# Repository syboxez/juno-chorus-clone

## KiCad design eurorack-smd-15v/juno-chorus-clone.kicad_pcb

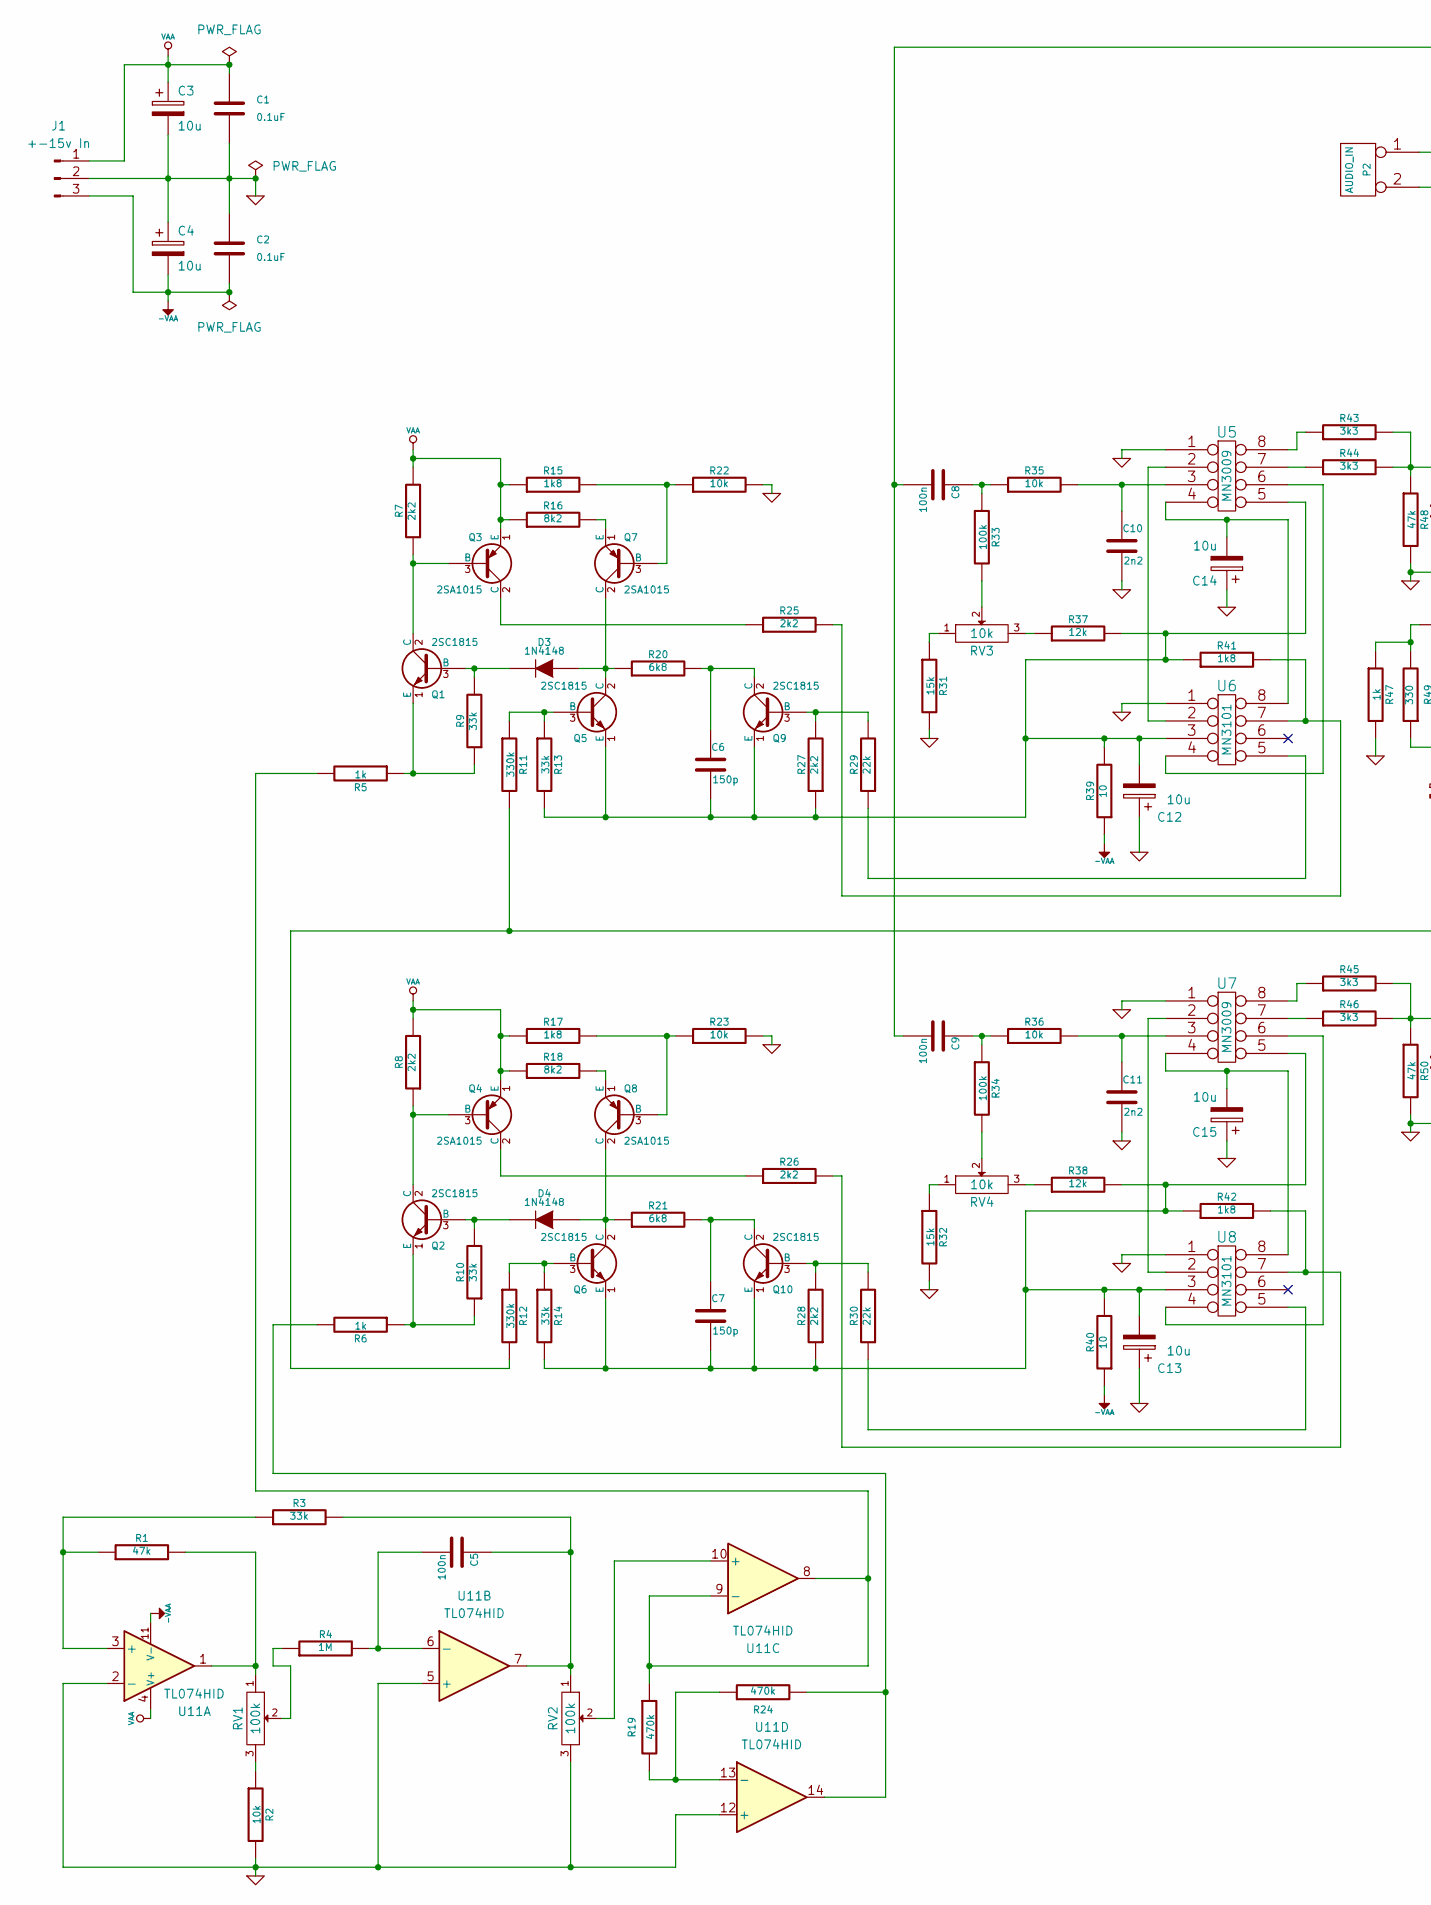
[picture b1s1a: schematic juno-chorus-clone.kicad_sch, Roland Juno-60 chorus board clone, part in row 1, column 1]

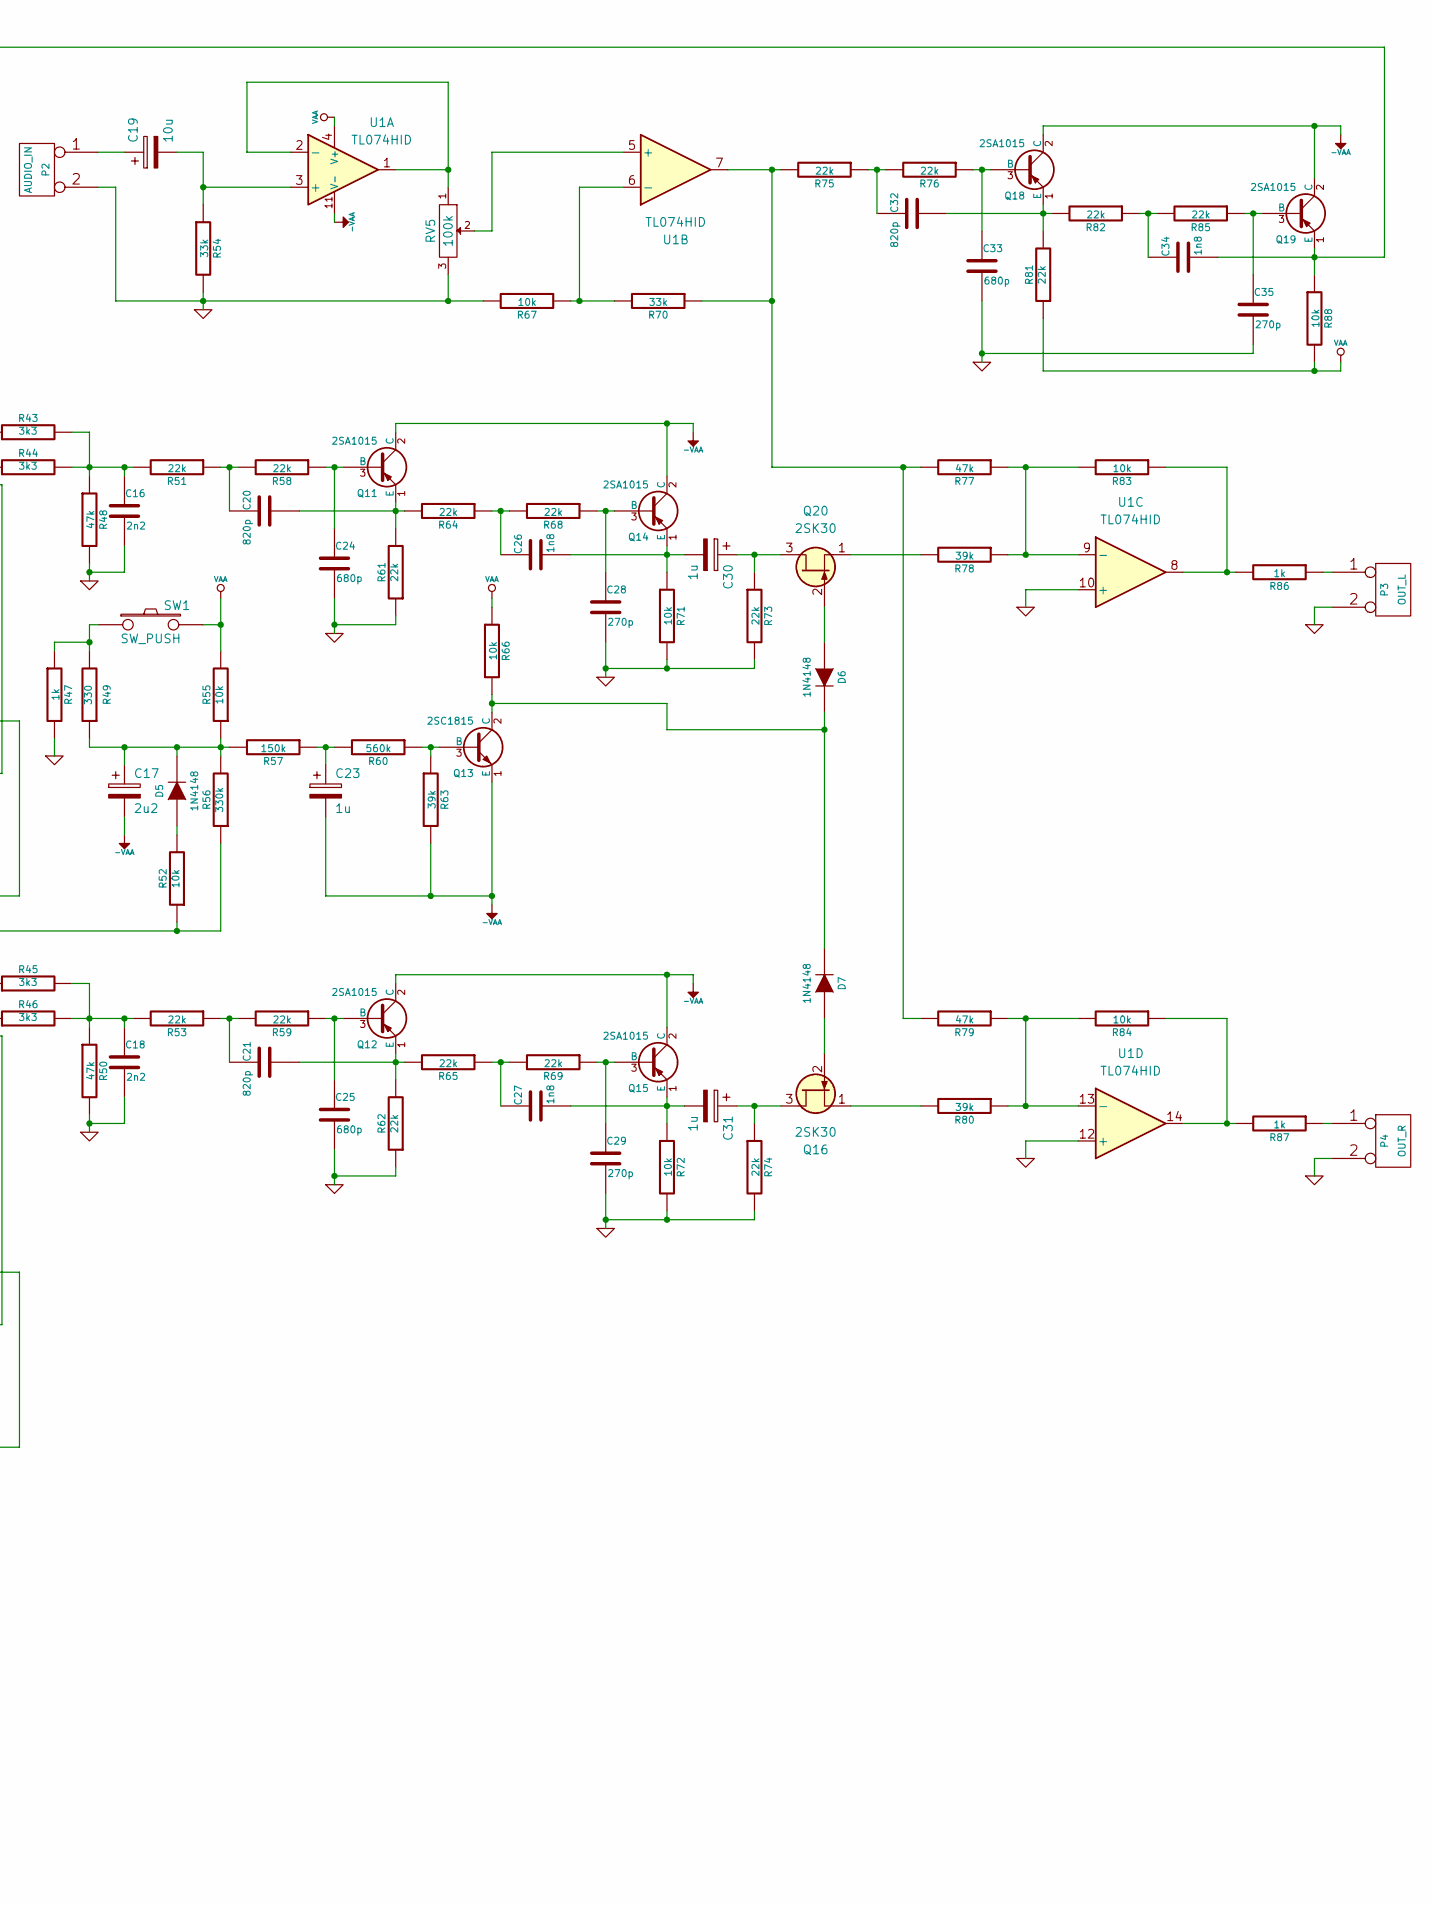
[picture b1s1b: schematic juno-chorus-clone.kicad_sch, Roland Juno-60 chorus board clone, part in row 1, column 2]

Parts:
C1, C2: 0.1uF; C_0805_2012Metric_Pad1.18x1.45mm_HandSolder
C3, C4, C12, C13, C14, C15, C19: 10u; CP_Radial_D5.0mm_P2.50mm
C5, C8, C9: 100n; C_0805_2012Metric_Pad1.18x1.45mm_HandSolder
C6, C7: 150p; C_0805_2012Metric_Pad1.18x1.45mm_HandSolder
C10, C11, C16, C18: 2n2; C_0805_2012Metric_Pad1.18x1.45mm_HandSolder
C17: 2u2; CP_Radial_D5.0mm_P2.50mm
C20, C21, C32: 820p; C_0805_2012Metric_Pad1.18x1.45mm_HandSolder
C23, C30, C31: 1u; CP_Radial_D5.0mm_P2.50mm
C24, C25, C33: 680p; C_0805_2012Metric_Pad1.18x1.45mm_HandSolder
C26, C27, C34: 1n8; C_0805_2012Metric_Pad1.18x1.45mm_HandSolder
C28, C29, C35: 270p; C_0805_2012Metric_Pad1.18x1.45mm_HandSolder
D3, D4, D5, D6, D7: 1N4148; D_0805_2012Metric_Pad1.15x1.40mm_HandSolder
J1: +-15v In; JST_XH_B3B-XH-A_1x03_P2.50mm_Vertical
P2: AUDIO_IN; JST_XH_B2B-XH-A_1x02_P2.50mm_Vertical
P3: OUT_L; JST_XH_B2B-XH-A_1x02_P2.50mm_Vertical
P4: OUT_R; JST_XH_B2B-XH-A_1x02_P2.50mm_Vertical
Q1, Q2, Q5, Q6, Q9, Q10, Q13: 2SC1815; TO-92_Inline_Wide
Q3, Q4, Q7, Q8, Q11, Q12, Q14, Q15, Q18, Q19: 2SA1015; TO-92_Inline_Wide
Q16, Q20: 2SK30; TO-92_Inline_Wide_SGD
R1, R48, R50, R77, R79: 47k; R_0805_2012Metric_Pad1.20x1.40mm_HandSolder
R2, R22, R23, R35, R36, R52, R55, R66, R67, R71, R72, R83, R84, R88: 10k; R_0805_2012Metric_Pad1.20x1.40mm_HandSolder
R3, R9, R10, R13, R14, R54, R70: 33k; R_0805_2012Metric_Pad1.20x1.40mm_HandSolder
R4: 1M; R_0805_2012Metric_Pad1.20x1.40mm_HandSolder
R5, R6, R47, R86, R87: 1k; R_0805_2012Metric_Pad1.20x1.40mm_HandSolder
R7, R8, R25, R26, R27, R28: 2k2; R_0805_2012Metric_Pad1.20x1.40mm_HandSolder
R11, R12, R56: 330k; R_0805_2012Metric_Pad1.20x1.40mm_HandSolder
R15, R17, R41, R42: 1k8; R_0805_2012Metric_Pad1.20x1.40mm_HandSolder
R16, R18: 8k2; R_0805_2012Metric_Pad1.20x1.40mm_HandSolder
R19, R24: 470k; R_0805_2012Metric_Pad1.20x1.40mm_HandSolder
R20, R21: 6k8; R_0805_2012Metric_Pad1.20x1.40mm_HandSolder
R29, R30, R51, R53, R58, R59, R61, R62, R64, R65, R68, R69, R73, R74, R75, R76, R81, R82, R85: 22k; R_0805_2012Metric_Pad1.20x1.40mm_HandSolder
R31, R32: 15k; R_0805_2012Metric_Pad1.20x1.40mm_HandSolder
R33, R34: 100k; R_0805_2012Metric_Pad1.20x1.40mm_HandSolder
R37, R38: 12k; R_0805_2012Metric_Pad1.20x1.40mm_HandSolder
R39, R40: 10; R_0805_2012Metric_Pad1.20x1.40mm_HandSolder
R43, R44, R45, R46: 3k3; R_0805_2012Metric_Pad1.20x1.40mm_HandSolder
R49: 330; R_0805_2012Metric_Pad1.20x1.40mm_HandSolder
R57: 150k; R_0805_2012Metric_Pad1.20x1.40mm_HandSolder
R60: 560k; R_0805_2012Metric_Pad1.20x1.40mm_HandSolder
R63, R78, R80: 39k; R_0805_2012Metric_Pad1.20x1.40mm_HandSolder
RV1, RV2, RV5: 100k; JST_XH_B3B-XH-A_1x03_P2.50mm_Vertical
RV3, RV4: 10k; Potentiometer_Runtron_RM-065_Vertical
SW1: SW_PUSH; JST_XH_B2B-XH-A_1x02_P2.50mm_Vertical
U1, U11: TL074HID; SOIC-14_3.9x8.7mm_P1.27mm
U5, U7: MN3009; DIP-8_W7.62mm_Socket_LongPads
U6, U8: MN3101; DIP-8_W7.62mm_Socket_LongPads

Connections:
-VAA: C2.2, C4.2, C17.2, C23.2, J1.3, Q11.2 (C), Q12.2 (C), Q13.1 (E), Q14.2 (C), Q15.2 (C), Q18.2 (C), Q19.2 (C), R39.1, R40.1, R63.2, U1.11 (V-), U11.11 (V-)
GND: C1.2, C2.1, C3.2, C4.1, C10.2, C11.2, C12.1, C13.1, C14.1, C15.1, C16.2, C18.2, C24.2, C25.2, C28.2, C29.2, C33.2, C35.2, J1.2, P2.2 (PM), P3.2 (PM), P4.2 (PM), R2.2, R22.2, R23.2, R31.2, R32.2, R47.2, R48.2, R50.2, R54.2, R61.1, R62.1, R67.2, R71.2, R72.2, R73.2, R74.2, RV2.3, RV5.3, U1.10 (+), U1.12 (+), U5.1, U6.1, U7.1, U8.1, U11.2 (-), U11.5 (+), U11.12 (+)
unnamed: C5.1, R3.2, RV2.1, U11.7
unnamed: C8.1, R33.1, R35.1
unnamed: C9.1, R34.1, R36.1
unnamed: C16.1, R43.2, R44.2, R48.1, R51.2
unnamed: C18.1, R45.2, R46.2, R50.1, R53.2
unnamed: C20.1, R51.1, R58.2
unnamed: C21.1, R53.1, R59.2
unnamed: C23.1, R57.1, R60.2
unnamed: C26.1, R64.1, R68.2
unnamed: C27.1, R65.1, R69.2
unnamed: C32.1, R75.1, R76.2
unnamed: C34.1, R82.1, R85.2
unnamed: D3.1 (A), Q5.2 (C), Q7.2 (C), R20.1
unnamed: D3.2 (K), Q1.3 (B), R9.2
unnamed: D4.1 (A), Q6.2 (C), Q8.2 (C), R21.1
unnamed: D4.2 (K), Q2.3 (B), R10.2
unnamed: D5.1 (A), R52.2
unnamed: C17.1, D5.2 (K), R49.1, R55.1, R56.2, R57.2
unnamed: D6.1 (A), Q20.2 (G)
unnamed: D6.2 (K), D7.2 (K), Q13.2 (C), R66.2
unnamed: D7.1 (A), Q16.2 (G)
unnamed: C19.1, P2.1
unnamed: P3.1, R86.1
unnamed: P4.1, R87.1
unnamed: Q1.2 (C), Q3.3 (B), R7.1
unnamed: Q1.1 (E), R5.1, R9.1
unnamed: Q2.2 (C), Q4.3 (B), R8.1
unnamed: Q2.1 (E), R6.1, R10.1
unnamed: Q3.2 (C), R25.1
unnamed: Q4.2 (C), R26.1
unnamed: Q5.3 (B), R11.1, R13.1
unnamed: C6.2, C12.2, Q5.1 (E), Q9.1 (E), R13.2, R27.1, R37.2, R39.2, R41.1, U5.5, U6.3
unnamed: Q6.3 (B), R12.1, R14.1
unnamed: Q7.3 (B), R15.2, R22.1
unnamed: Q7.1 (E), R16.2
unnamed: Q8.3 (B), R17.2, R23.1
unnamed: Q8.1 (E), R18.2
unnamed: Q9.3 (B), R27.2, R29.2
unnamed: C6.1, Q9.2 (C), R20.2
unnamed: Q10.3 (B), R28.2, R30.2
unnamed: C7.1, Q10.2 (C), R21.2
unnamed: C7.2, C13.2, Q6.1 (E), Q10.1 (E), R14.2, R28.1, R38.2, R40.2, R42.1, U7.5, U8.3
unnamed: C24.1, Q11.3 (B), R58.1
unnamed: C20.2, Q11.1 (E), R61.2, R64.2
unnamed: C25.1, Q12.3 (B), R59.1
unnamed: C21.2, Q12.1 (E), R62.2, R65.2
unnamed: Q13.3 (B), R60.1, R63.1
unnamed: C28.1, Q14.3 (B), R68.1
unnamed: C26.2, C30.2, Q14.1 (E), R71.1
unnamed: C29.1, Q15.3 (B), R69.1
unnamed: C27.2, C31.2, Q15.1 (E), R72.1
unnamed: C31.1, Q16.3 (D), R74.1
unnamed: Q16.1 (S), R80.2
unnamed: C33.1, Q18.3 (B), R76.1
unnamed: C32.2, Q18.1 (E), R81.2, R82.2
unnamed: C35.1, Q19.3 (B), R85.1
unnamed: C8.2, C9.2, C34.2, Q19.1 (E), R88.1
unnamed: C30.1, Q20.3 (D), R73.1
unnamed: Q20.1 (S), R78.2
unnamed: R1.2, RV1.1, U11.1
unnamed: R2.1, RV1.3
unnamed: R4.1, RV1.2
unnamed: R11.2, R12.2, R52.1, R56.1
unnamed: R6.2, R24.2, U11.14
unnamed: R31.1, RV3.1
unnamed: R32.1, RV4.1
unnamed: R33.2, RV3.2
unnamed: R34.2, RV4.2
unnamed: R37.1, RV3.3
unnamed: R38.1, RV4.3
unnamed: R47.1, R49.2, SW1.1
unnamed: R70.1, R75.2, R77.2, R79.2, U1.7
unnamed: R83.1, R86.2, U1.8
unnamed: R84.1, R87.2, U1.14
unnamed: C19.2, R54.1, U1.3 (+)
unnamed: RV5.1, U1.1, U1.2 (-)
unnamed: RV5.2, U1.5 (+)
unnamed: R67.1, R70.2, U1.6 (-)
unnamed: R77.1, R78.1, R83.2, U1.9 (-)
unnamed: R79.1, R80.1, R84.2, U1.13 (-)
unnamed: U5.2, U6.2
unnamed: C10.1, R35.2, U5.3
unnamed: C14.2, U5.4, U6.8
unnamed: U5.6, U6.4
unnamed: R44.1, U5.7
unnamed: R43.1, U5.8
unnamed: R29.1, U6.5
unnamed: R25.2, R41.2, U6.7
unnamed: U7.2, U8.2
unnamed: C11.1, R36.2, U7.3
unnamed: C15.2, U7.4, U8.8
unnamed: U7.6, U8.4
unnamed: R46.1, U7.7
unnamed: R45.1, U7.8
unnamed: R30.1, U8.5
unnamed: R26.2, R42.2, U8.7
unnamed: R1.1, R3.1, U11.3 (+)
unnamed: C5.2, R4.2, U11.6 (-)
unnamed: RV2.2, U11.10 (+)
unnamed: R5.2, R19.1, U11.8, U11.9 (-)
unnamed: R19.2, R24.1, U11.13 (-)
VAA: C1.1, C3.1, J1.1, Q3.1 (E), Q4.1 (E), R7.2, R8.2, R15.1, R16.1, R17.1, R18.1, R55.2, R66.1, R81.1, R88.2, SW1.2, U1.4 (V+), U11.4 (V+)

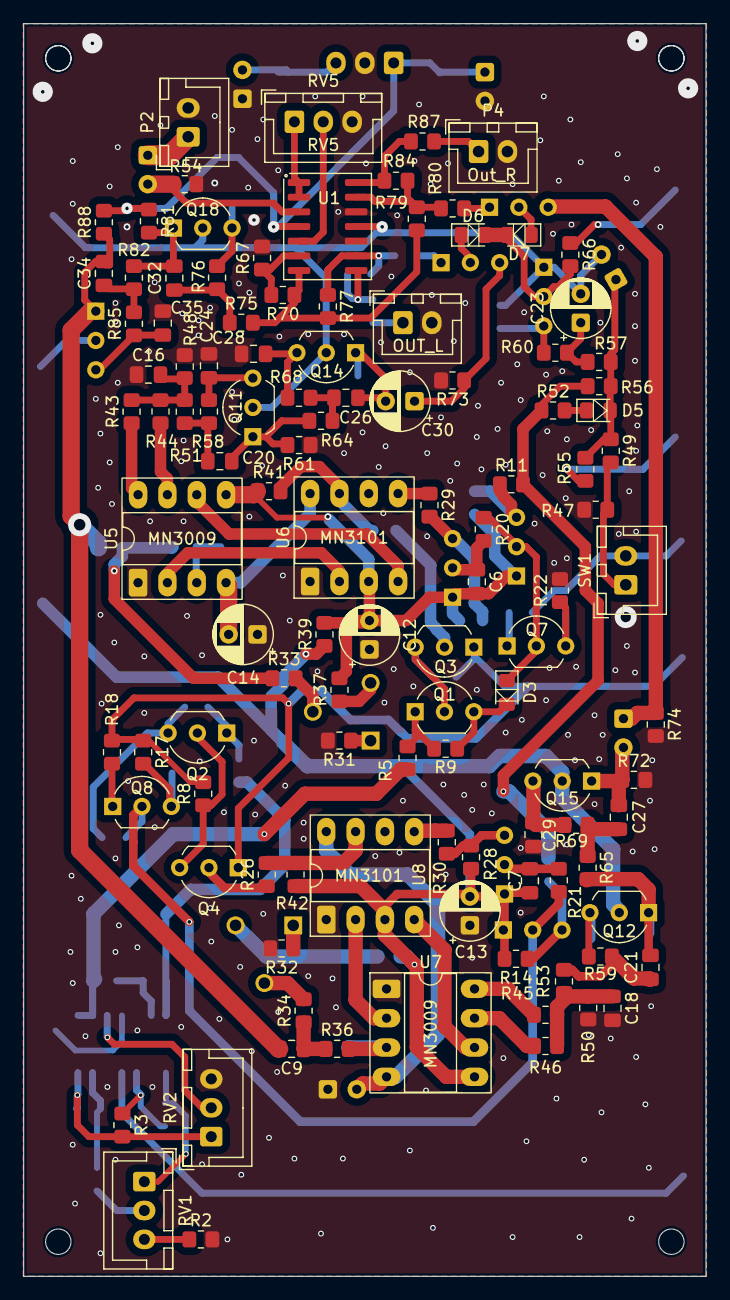
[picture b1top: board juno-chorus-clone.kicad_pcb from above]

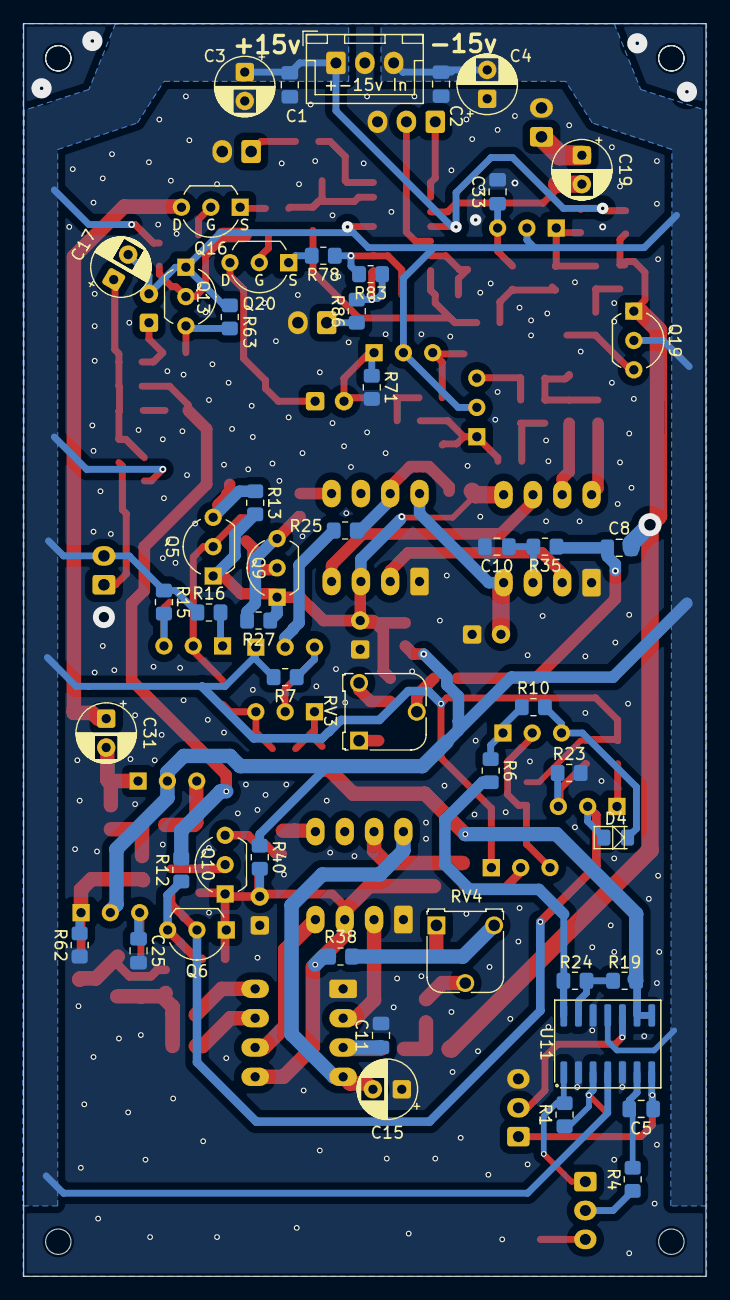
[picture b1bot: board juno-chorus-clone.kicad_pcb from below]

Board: 2 copper layers, 59.1 x 108.5 mm, 162 parts (50 on the bottom side), 104 nets.

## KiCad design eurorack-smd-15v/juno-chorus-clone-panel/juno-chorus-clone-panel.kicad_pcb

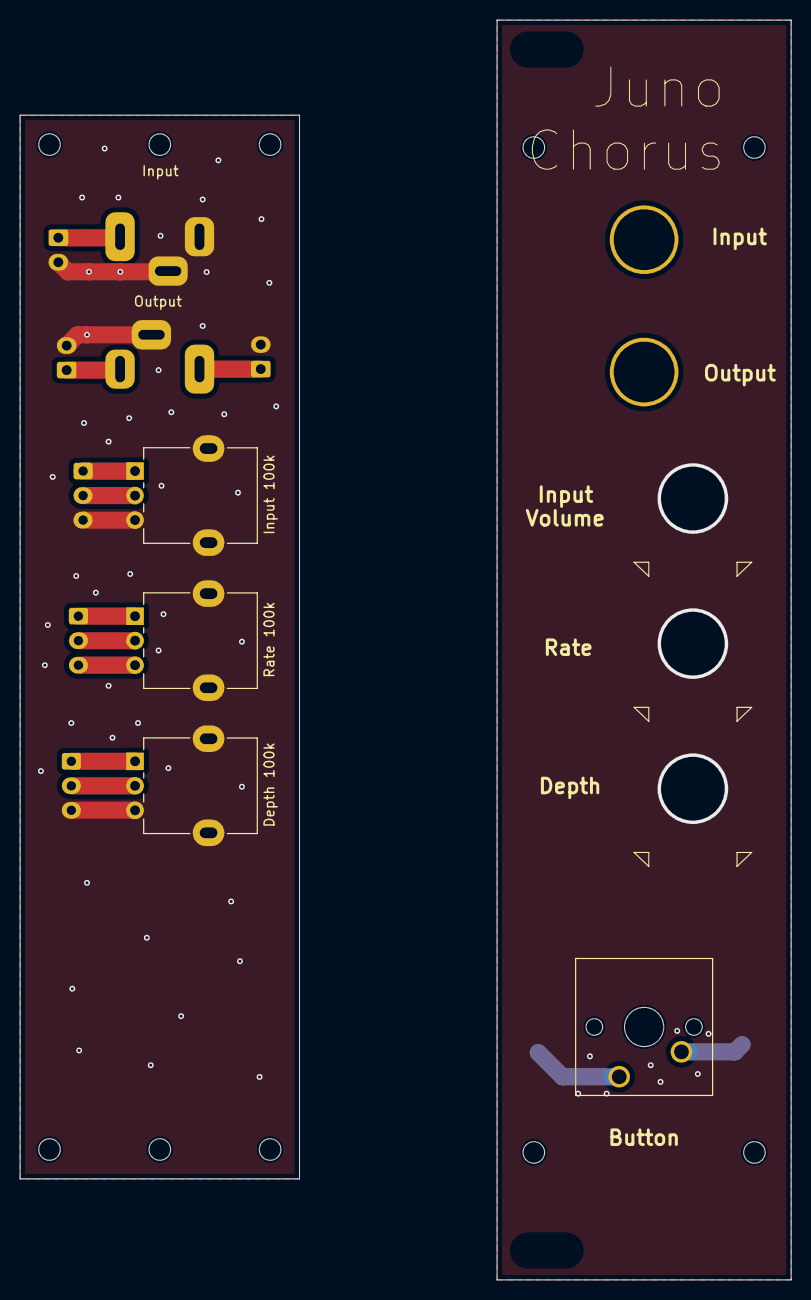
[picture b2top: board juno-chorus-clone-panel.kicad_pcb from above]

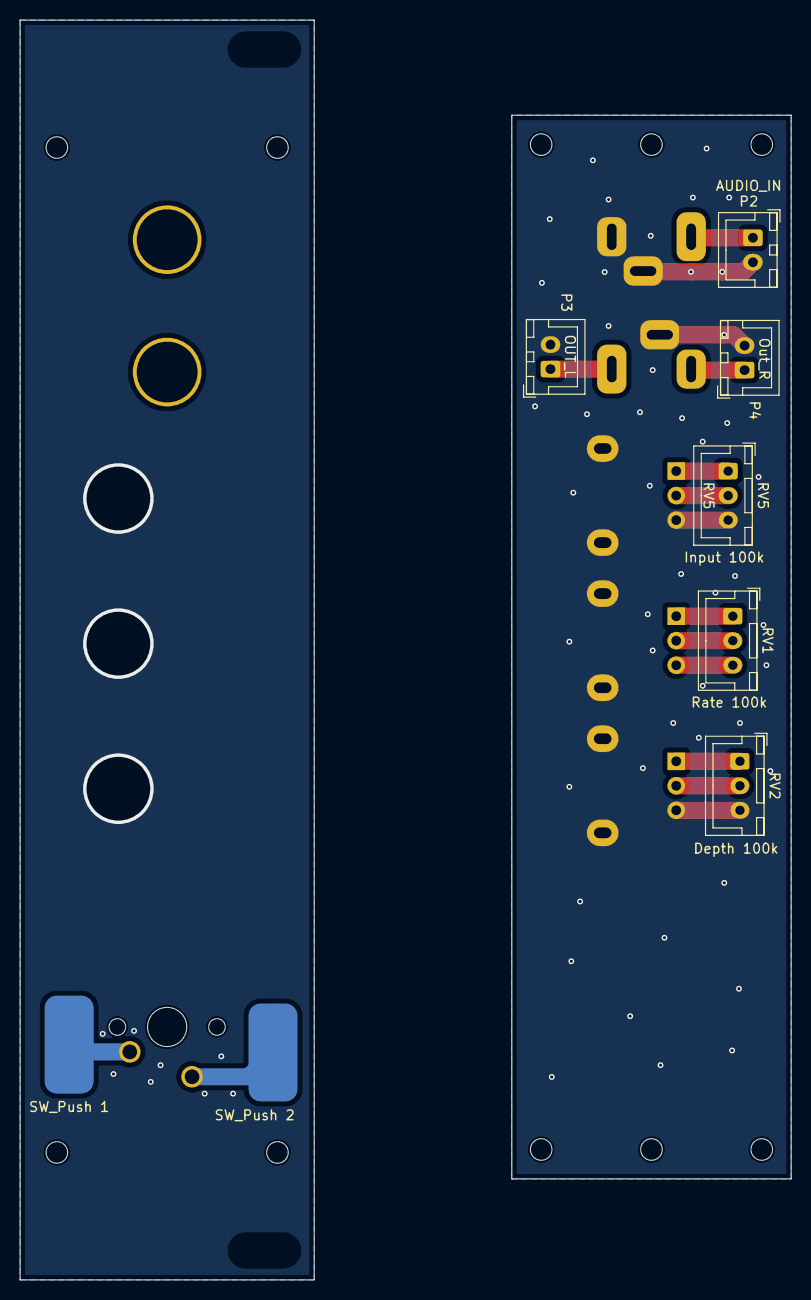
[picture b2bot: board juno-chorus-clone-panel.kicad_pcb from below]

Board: 2 copper layers, 78.6 x 128.5 mm, 14 parts (8 on the bottom side), 13 nets.

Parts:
Button: SW_Cherry_MX_1.00u_PCB
Input: SJ3-35053A; Jack_3.5mm_SJ3-35053A_Vertical
J1: SW_Push 1; SolderWirePad_1x01_SMD_5x10mm
J2: SW_Push 2; SolderWirePad_1x01_SMD_5x10mm
Output: SJ3-35053A; Jack_3.5mm_SJ3-35053A_Vertical
P2: AUDIO_IN; JST_XH_B2B-XH-A_1x02_P2.50mm_Vertical
P3: OUT_L; JST_XH_B2B-XH-A_1x02_P2.50mm_Vertical
P4: Out_R; JST_XH_B2B-XH-A_1x02_P2.50mm_Vertical
POT1: Rate 100k; Potentiometer_Alpha_RD901F-40-00D_Single_Vertical
POT1#2: Input 100k; Potentiometer_Alpha_RD901F-40-00D_Single_Vertical
POT1#3: Depth 100k; Potentiometer_Alpha_RD901F-40-00D_Single_Vertical
RV1: Rate 100k; JST_XH_B3B-XH-A_1x03_P2.50mm_Vertical
RV2: Depth 100k; JST_XH_B3B-XH-A_1x03_P2.50mm_Vertical
RV5: Input 100k; JST_XH_B3B-XH-A_1x03_P2.50mm_Vertical

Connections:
GND: Input.R, Input.S, Output.S, P2.2 (PM), P3.2 (PM), P4.2 (PM), POT1#2.3, POT1#3.3, RV2.3, RV5.3
unnamed: POT1#3.1, RV2.1
unnamed: Input.T, P2.1
unnamed: Output.T, P3.1
unnamed: Output.R, P4.1
unnamed: POT1.1, RV1.1
unnamed: POT1.3, RV1.3
unnamed: POT1.2, RV1.2
unnamed: Button.2, J1.1
unnamed: POT1#2.1, RV5.1
unnamed: POT1#2.2, RV5.2
unnamed: POT1#3.2, RV2.2
VAA: Button.1, J2.1

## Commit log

2025-12-13 Add non-standard Eurorack (15v) PCB using some SMD components to reduce size
2025-12-14 Add ground plane to GliGli's through hole PCB
2025-12-14 Remove legacy KiCad files
2025-12-14 Add Eurorack-style Panel
2025-12-17 Replace TL084 with TL074 to stay consistent with my other designs
